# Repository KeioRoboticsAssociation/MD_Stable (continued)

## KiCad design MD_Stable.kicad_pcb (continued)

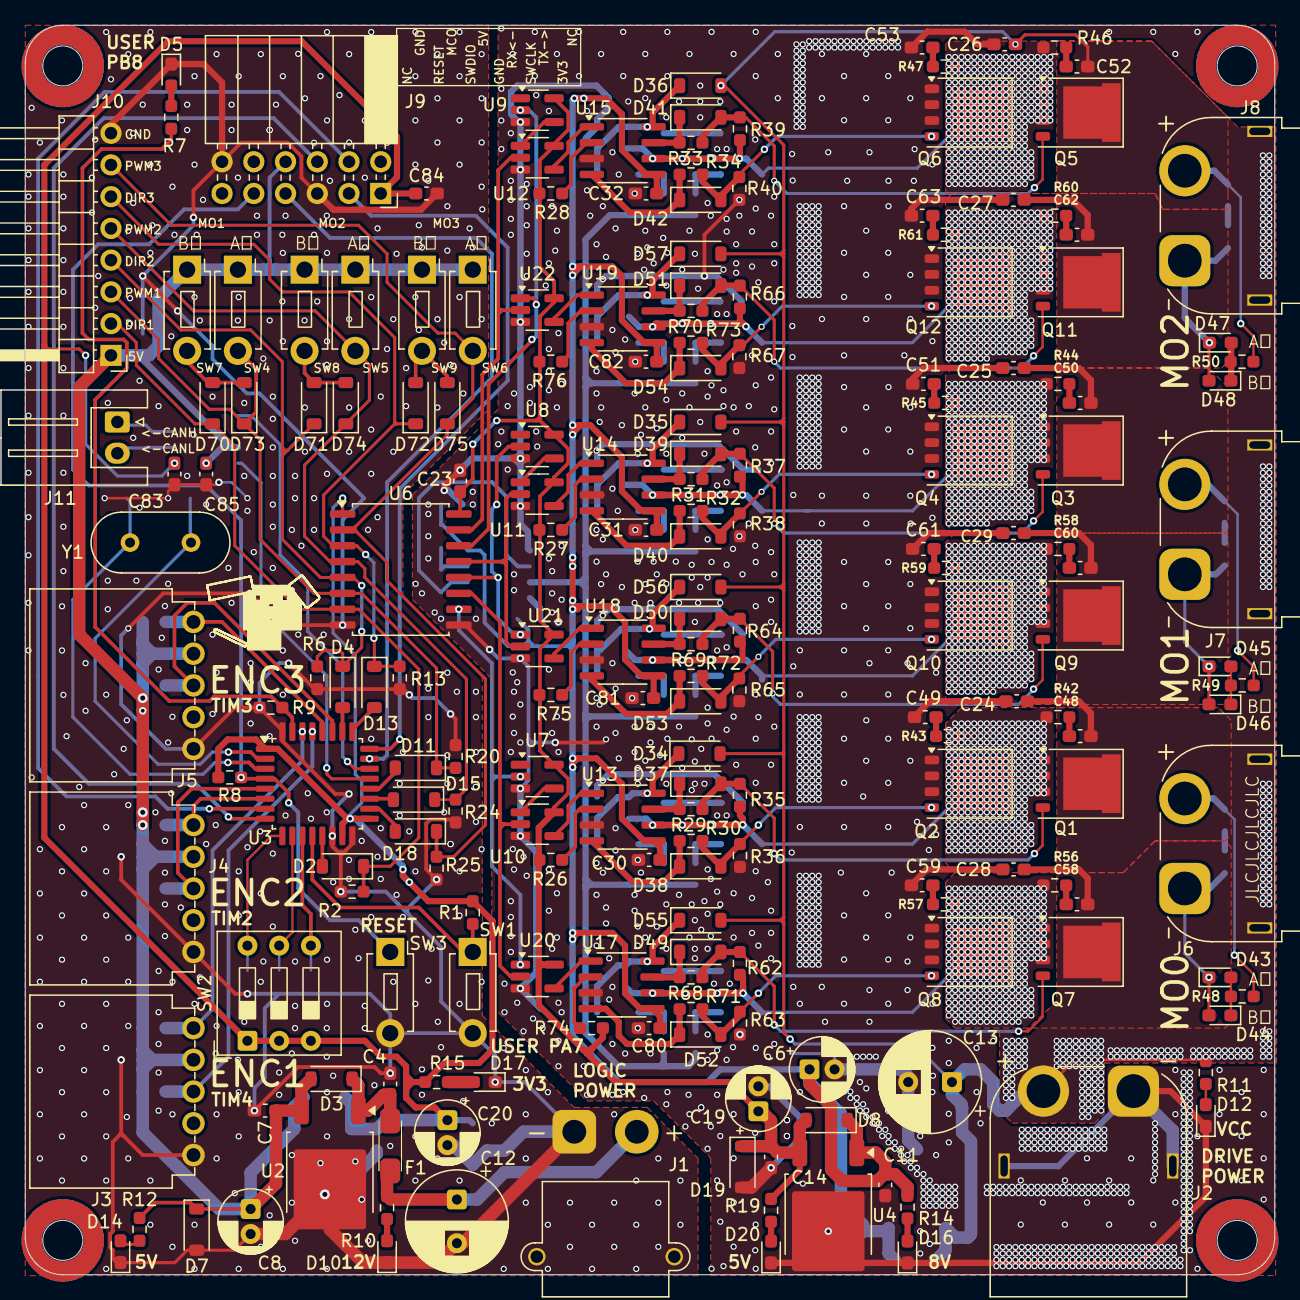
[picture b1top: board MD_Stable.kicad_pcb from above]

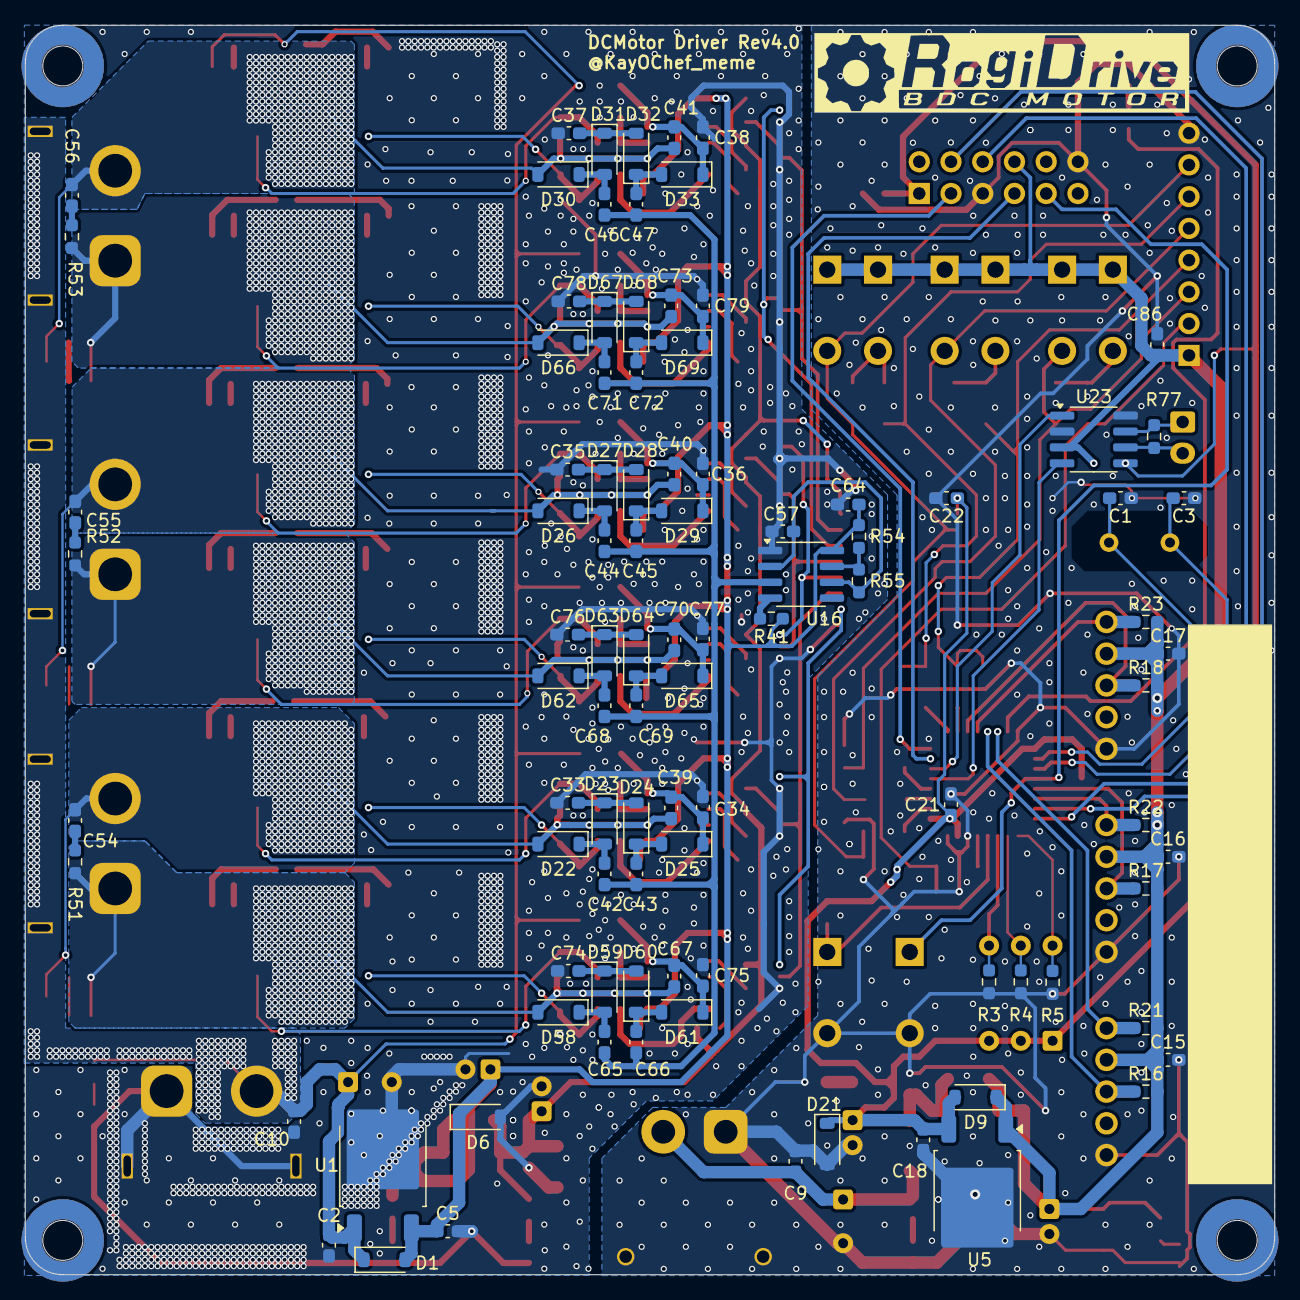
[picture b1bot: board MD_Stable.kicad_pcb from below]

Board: 2 copper layers, 100.0 x 100.0 mm, 296 parts (96 on the bottom side), 150 nets.

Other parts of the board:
ref**: val**; ROGIKEN

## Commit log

2025-09-25 がちでgit使えるやん
2025-09-25 電装班がGitHubに上陸
2025-10-01 回路図おおむね完成
2025-10-02 配線し始めた
2025-10-03 配線終わり見えてきた
2025-10-05 MD基板完成
2025-10-14 製造番号位置指定
2025-11-27 rev3.1
2025-11-28 配線修正
2026-01-08 RS485Tx fix
2026-04-28 beyond the MD10C Rev4.0
2026-05-03 時代はね、CANなんすよ
